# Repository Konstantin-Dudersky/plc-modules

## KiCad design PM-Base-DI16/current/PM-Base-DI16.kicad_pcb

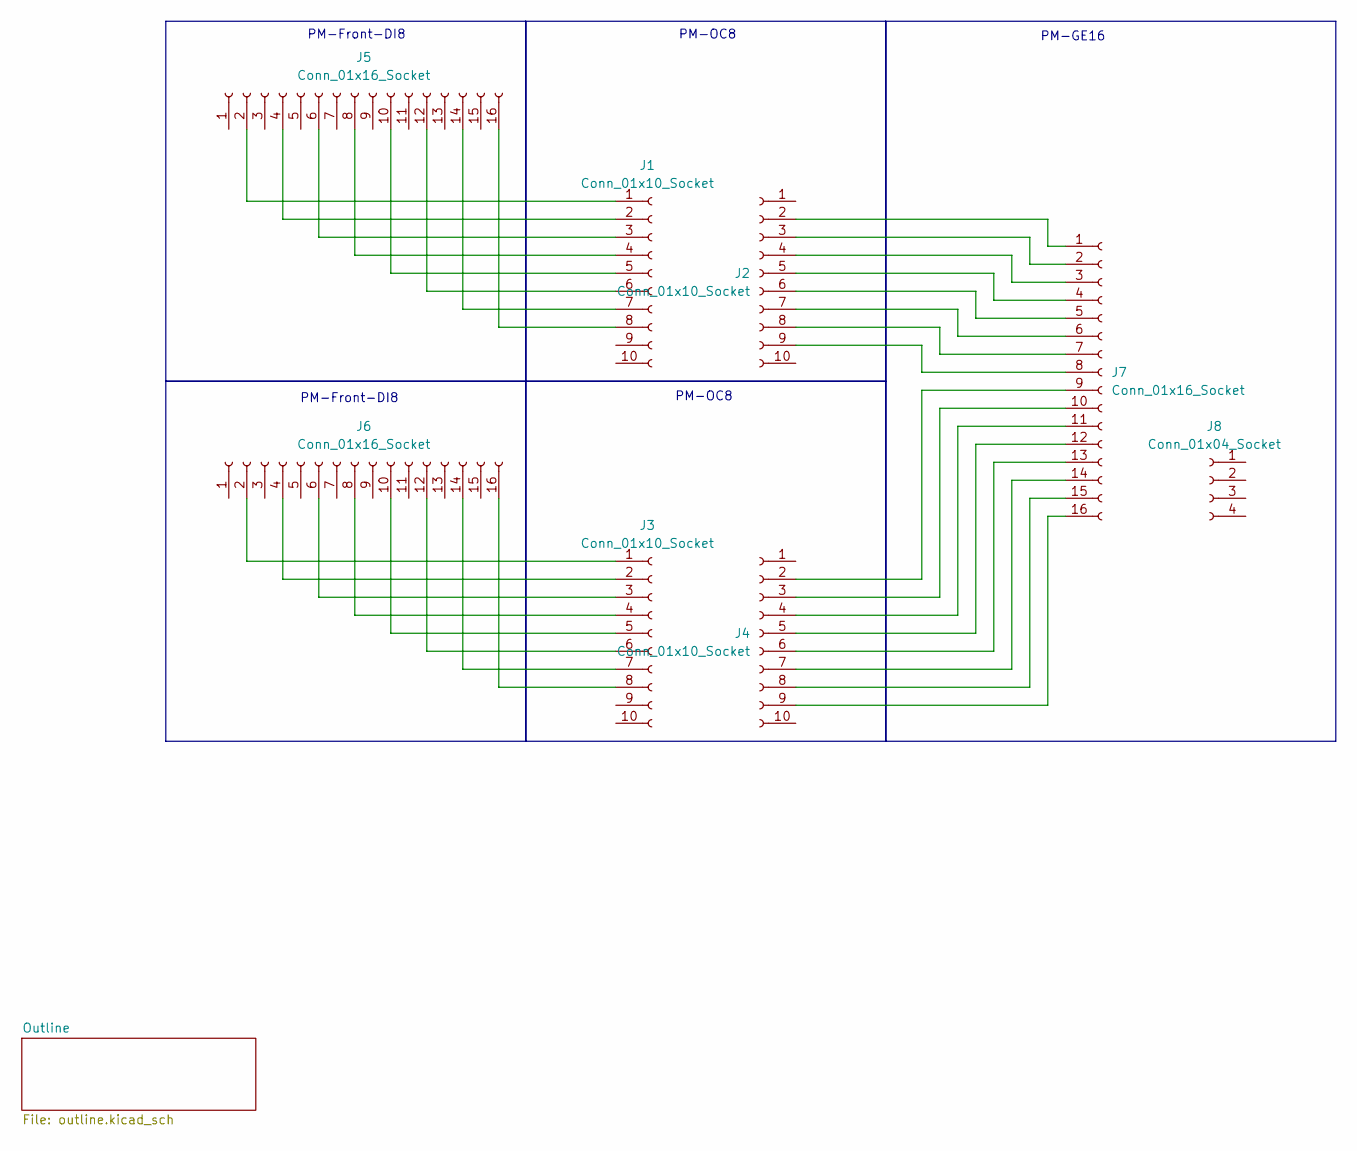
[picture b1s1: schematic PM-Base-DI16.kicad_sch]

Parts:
J1, J2, J3, J4: Conn_01x10_Socket; PinSocket_1x10_P2.54mm_Vertical_SMD_Pin1Left
J5, J6, J7: Conn_01x16_Socket; PinSocket_1x16_P2.54mm_Vertical_SMD_Pin1Left
J8: Conn_01x04_Socket; PinSocket_1x04_P2.54mm_Vertical_SMD_Pin1Left

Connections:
unnamed: J1.1, J5.2
unnamed: J1.2, J5.4
unnamed: J1.3, J5.6
unnamed: J1.4, J5.8
unnamed: J1.5, J5.10
unnamed: J1.6, J5.12
unnamed: J1.7, J5.14
unnamed: J1.8, J5.16
unnamed: J2.2, J7.1
unnamed: J2.3, J7.2
unnamed: J2.4, J7.3
unnamed: J2.5, J7.4
unnamed: J2.6, J7.5
unnamed: J2.7, J7.6
unnamed: J2.8, J7.7
unnamed: J2.9, J7.8
unnamed: J3.1, J6.2
unnamed: J3.2, J6.4
unnamed: J3.3, J6.6
unnamed: J3.4, J6.8
unnamed: J3.5, J6.10
unnamed: J3.6, J6.12
unnamed: J3.7, J6.14
unnamed: J3.8, J6.16
unnamed: J4.2, J7.9
unnamed: J4.3, J7.10
unnamed: J4.4, J7.11
unnamed: J4.5, J7.12
unnamed: J4.6, J7.13
unnamed: J4.7, J7.14
unnamed: J4.8, J7.15
unnamed: J4.9, J7.16

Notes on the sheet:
PM-OC8
PM-Front-DI8
PM-GE16

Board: 2 copper layers, 8 parts (0 on the bottom side), 32 nets, no tracks yet.

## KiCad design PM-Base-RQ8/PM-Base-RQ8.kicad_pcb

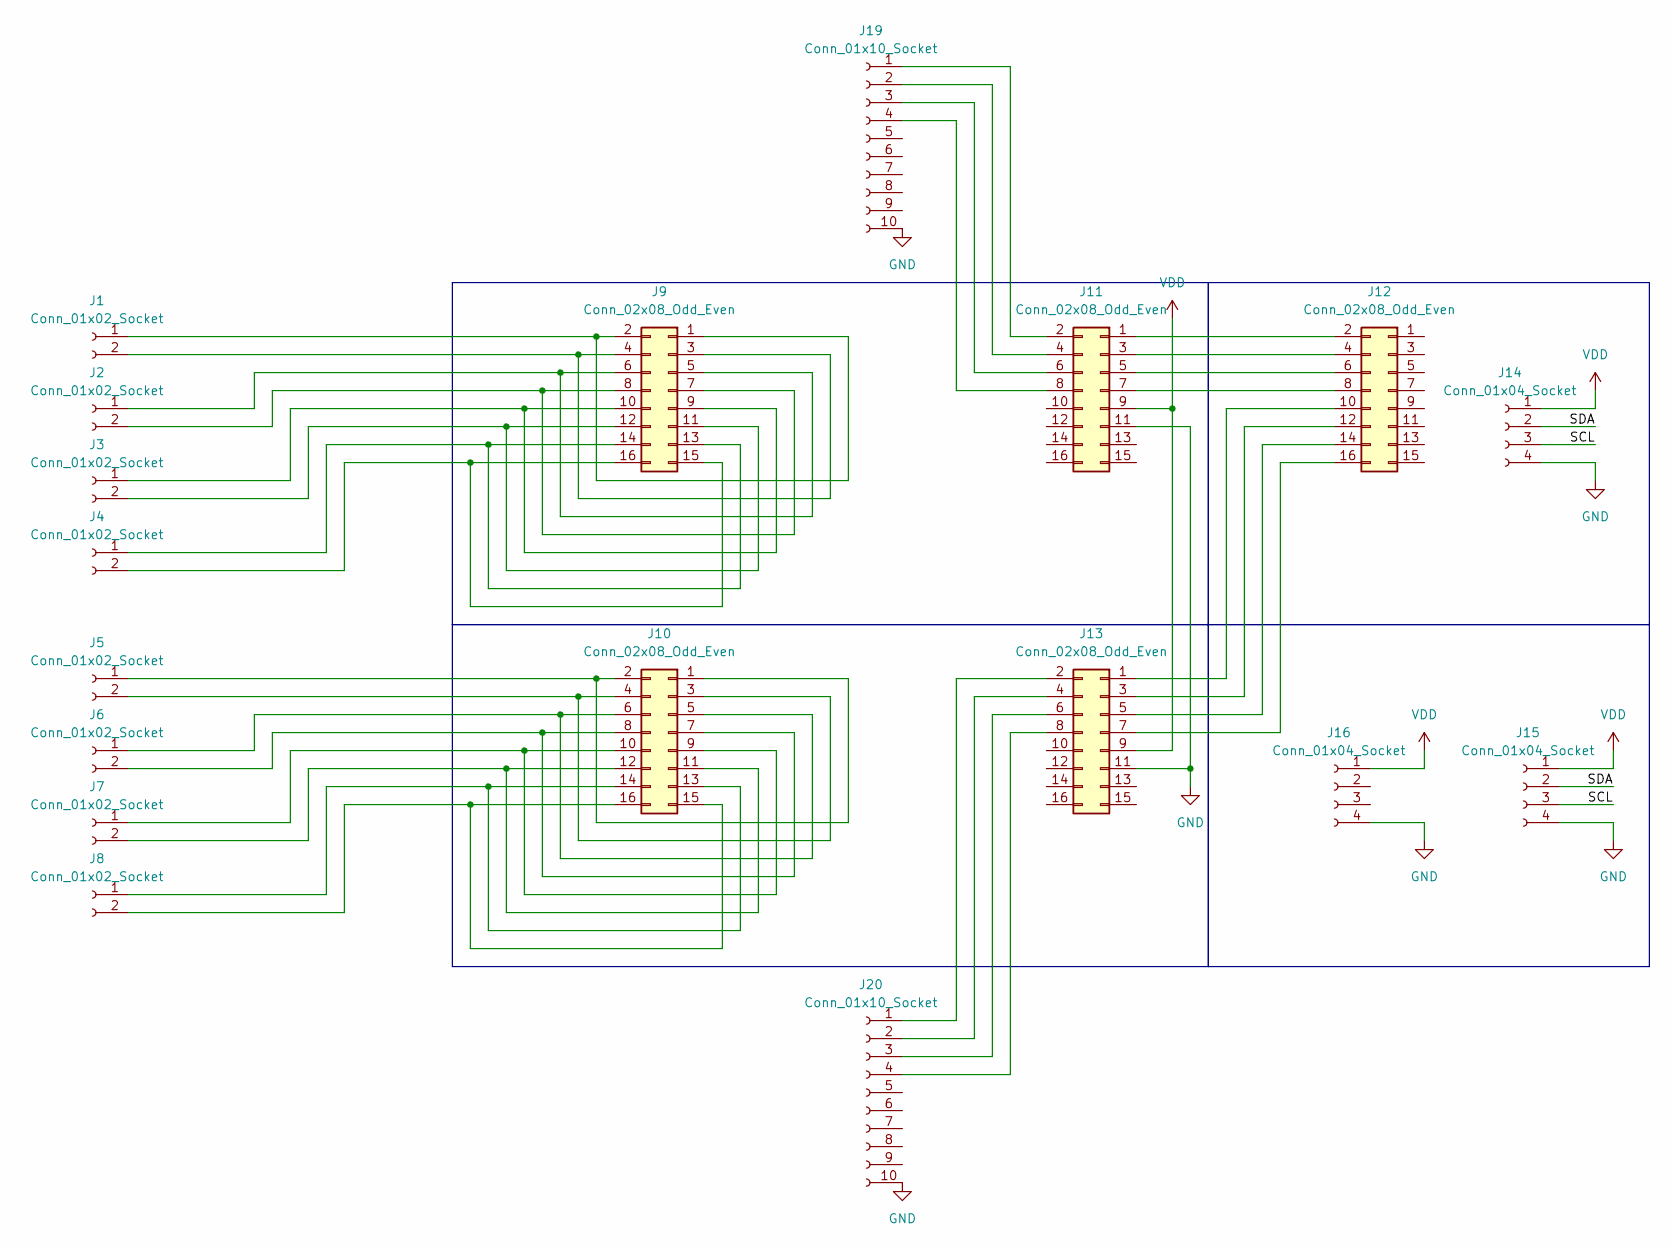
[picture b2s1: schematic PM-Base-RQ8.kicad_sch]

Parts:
J1, J2, J3, J4, J5, J6, J7, J8: Conn_01x02_Socket; Degson_2EDGK-5.08-02P
J9, J10, J11, J12, J13: Conn_02x08_Odd_Even; PinSocket_2x08_P2.54mm_Vertical_SMD
J14, J15, J16: Conn_01x04_Socket; PinSocket_1x04_P2.54mm_Vertical_SMD_Pin1Left
J19, J20: Conn_01x10_Socket; PinSocket_1x10_P2.54mm_Vertical_SMD_Pin1Left

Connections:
/SCL: J14.3, J15.3
/SDA: J14.2, J15.2
GND: J11.11, J13.11, J14.4, J15.4, J16.4, J19.10, J20.10
unnamed: J1.1, J9.1, J9.2
unnamed: J1.2, J9.3, J9.4
unnamed: J2.1, J9.5, J9.6
unnamed: J2.2, J9.7, J9.8
unnamed: J3.1, J9.9, J9.10
unnamed: J3.2, J9.11, J9.12
unnamed: J4.1, J9.13, J9.14
unnamed: J4.2, J9.15, J9.16
unnamed: J5.1, J10.1, J10.2
unnamed: J5.2, J10.3, J10.4
unnamed: J6.1, J10.5, J10.6
unnamed: J6.2, J10.7, J10.8
unnamed: J7.1, J10.9, J10.10
unnamed: J7.2, J10.11, J10.12
unnamed: J8.1, J10.13, J10.14
unnamed: J8.2, J10.15, J10.16
unnamed: J11.1, J12.2
unnamed: J11.2, J19.1
unnamed: J11.3, J12.4
unnamed: J11.4, J19.2
unnamed: J11.5, J12.6
unnamed: J11.6, J19.3
unnamed: J11.7, J12.8
unnamed: J11.8, J19.4
unnamed: J12.10, J13.1
unnamed: J12.12, J13.3
unnamed: J12.14, J13.5
unnamed: J12.16, J13.7
unnamed: J13.2, J20.1
unnamed: J13.4, J20.2
unnamed: J13.6, J20.3
unnamed: J13.8, J20.4
VDD: J11.9, J13.9, J14.1, J15.1, J16.1

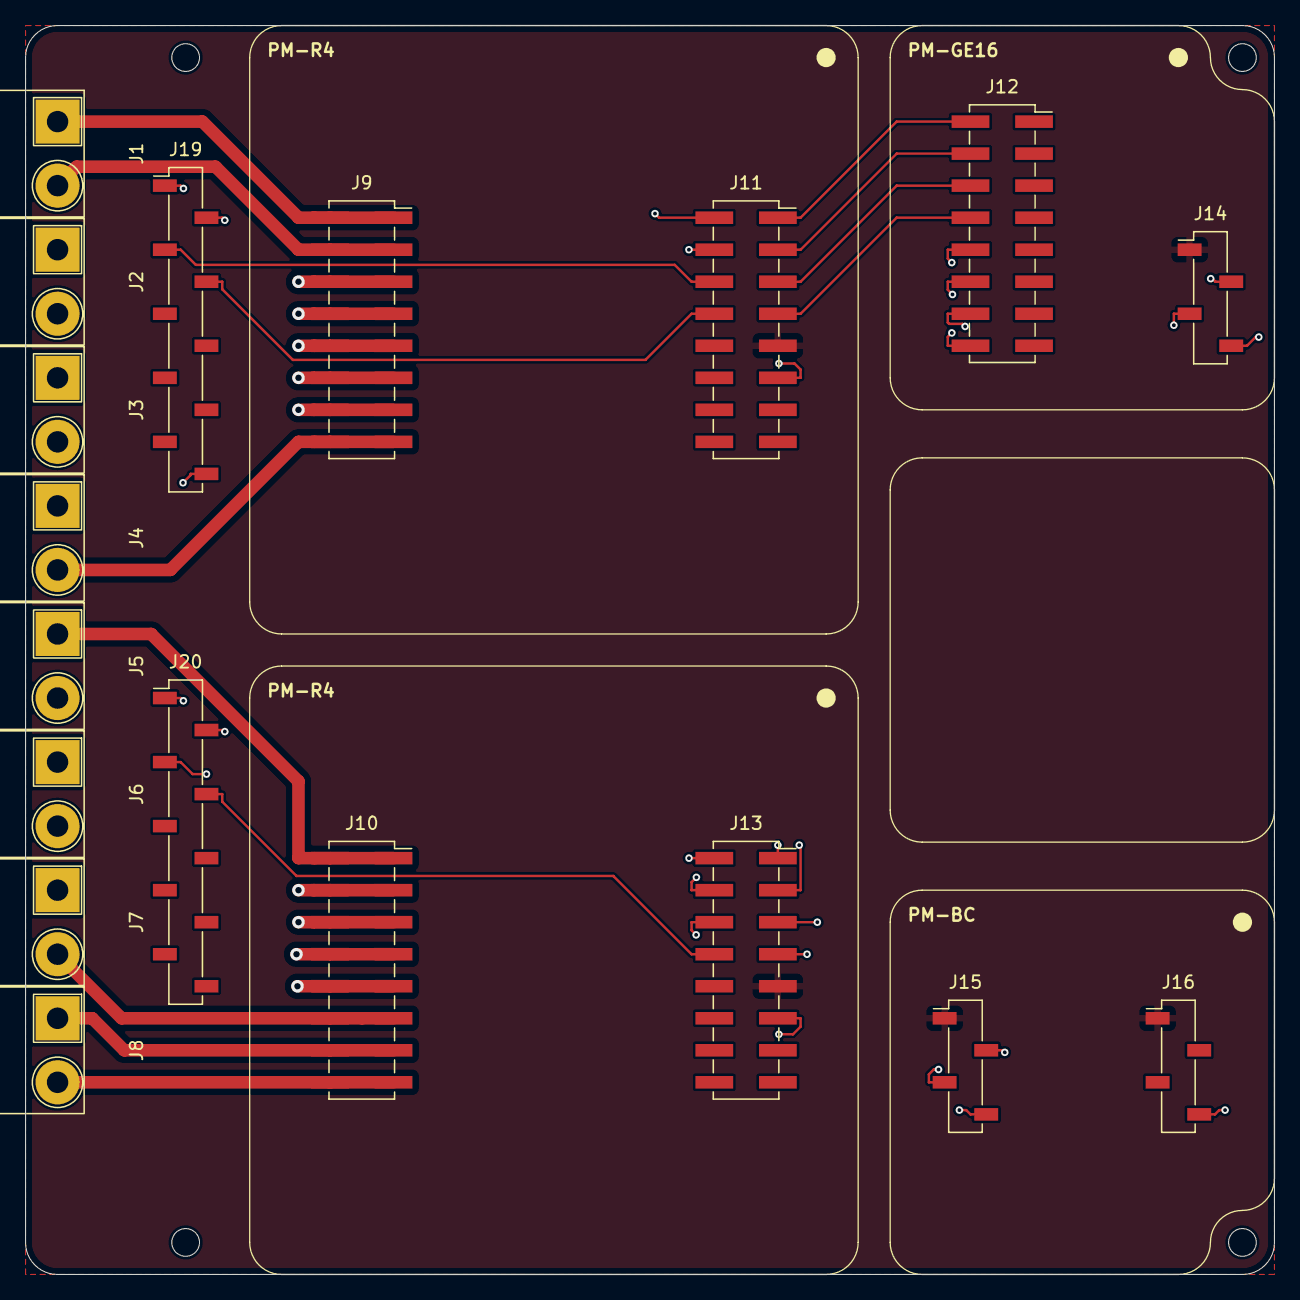
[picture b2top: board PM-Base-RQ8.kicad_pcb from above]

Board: 4 copper layers, 99.1 x 99.1 mm, 22 parts (0 on the bottom side), 36 nets.

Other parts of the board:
H1, H2, H3, H4: MountingHole_2.2mm_M2

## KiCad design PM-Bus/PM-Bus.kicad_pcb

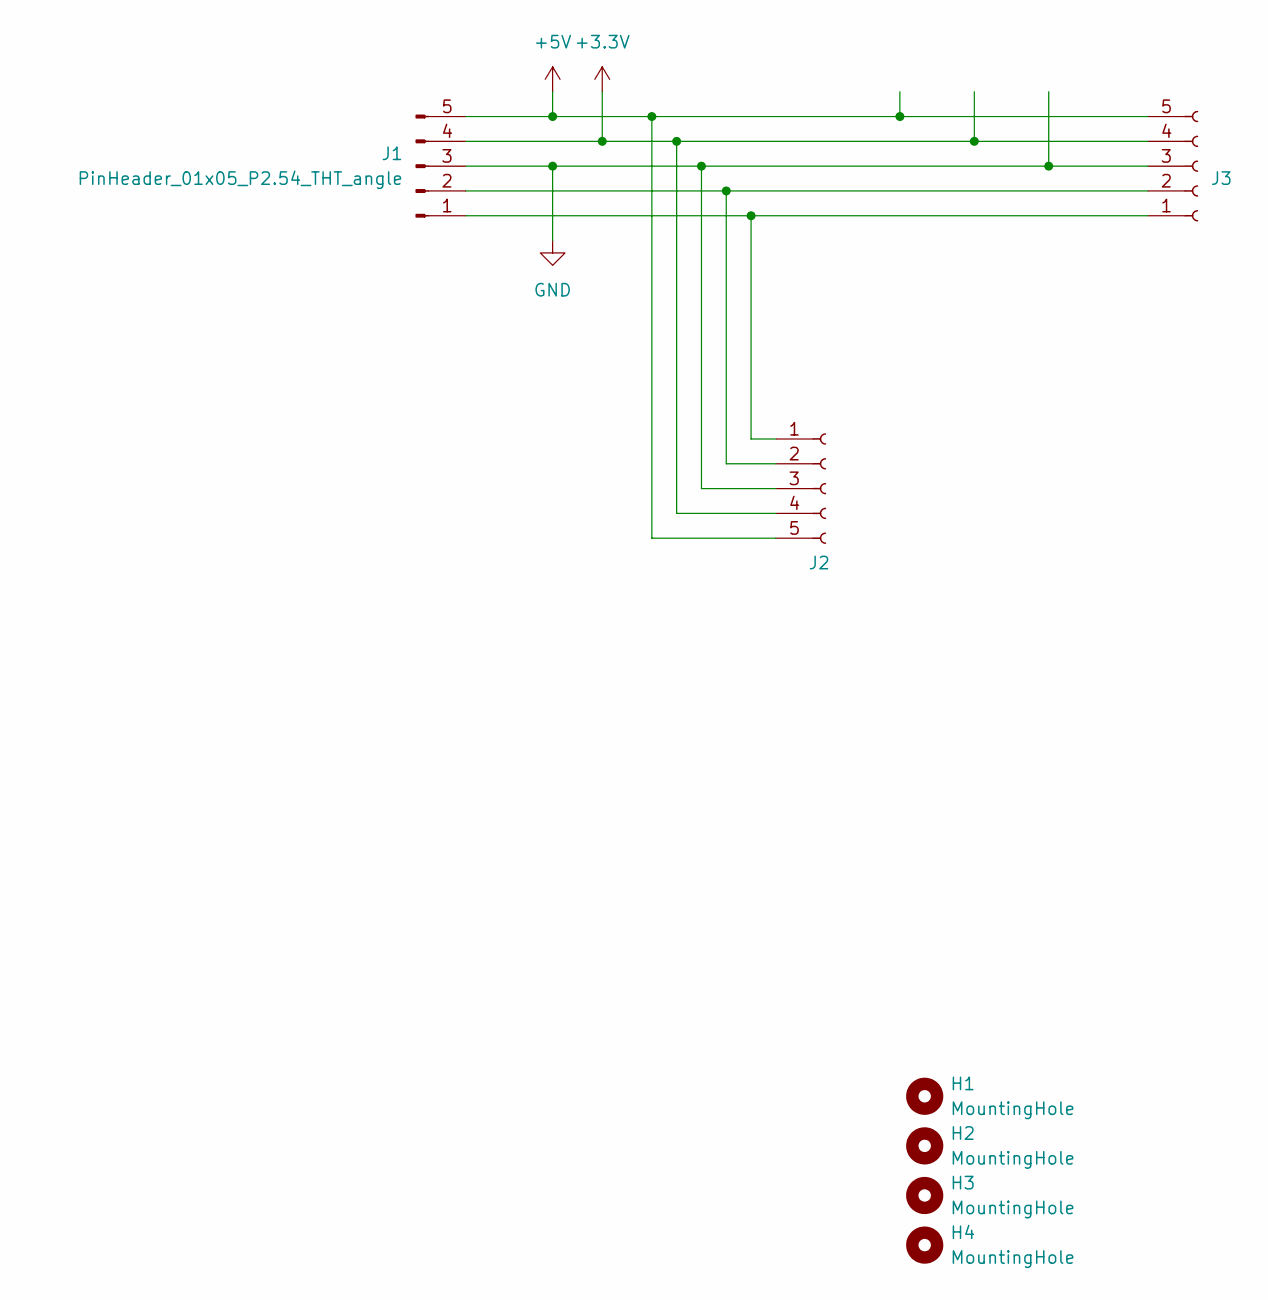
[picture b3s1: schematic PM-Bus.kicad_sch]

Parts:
H1, H2, H3, H4: MountingHole; MountingHole_3.2mm_M3
J1: PinHeader_01x05_P2.54_THT_angle; PinHeader_1x05_P2.54mm_Horizontal; part_ipn PinHeader_01x05_P2.54_THT_angle
J2: FemaleHeader_01x05_P2.54_THT_straight; PinSocket_1x05_P2.54mm_Vertical; part_ipn FemaleHeader_01x05_P2.54_THT_straight
J3: FemaleHeader_01x05_P2.54_THT_angle; PinSocket_1x05_P2.54mm_Horizontal; part_ipn FemaleHeader_01x05_P2.54_THT_angle

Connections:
+3.3V: J1.4, J2.4, J3.4
+5V: J1.5, J2.5, J3.5
GND: J1.3, J2.3, J3.3
unnamed: J1.1, J2.1, J3.1
unnamed: J1.2, J2.2, J3.2

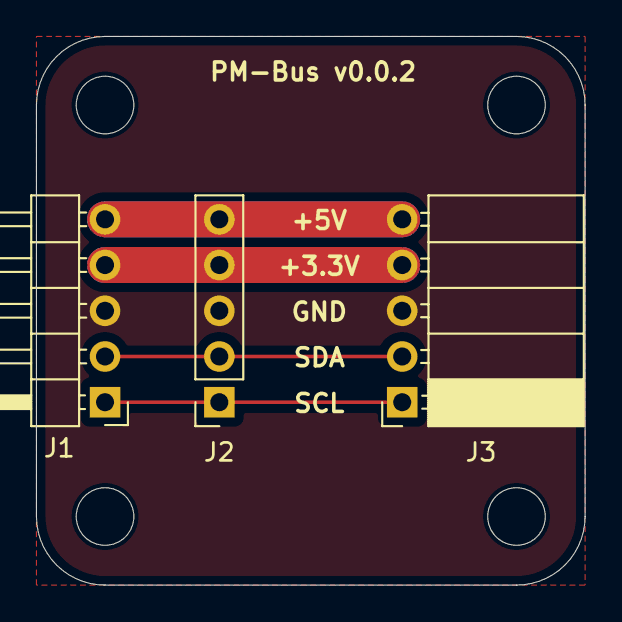
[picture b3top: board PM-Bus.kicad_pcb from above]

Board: 2 copper layers, 30.5 x 30.5 mm, 8 parts (1 on the bottom side), 5 nets.

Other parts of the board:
Logo_kicad: KiCad-Logo2_5mm_SilkScreen

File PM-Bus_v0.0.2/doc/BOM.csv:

"reference","note","quantity","part_ipn"
"J1","Generic connector, single row, 01x05, script generated","1","PinHeader_01x05_P2.54_THT_angle"
"J2","Generic connector, single row, 01x05, script generated","1","FemaleHeader_01x05_P2.54_THT_straight"
"J3","Generic connector, single row, 01x05, script generated","1","FemaleHeader_01x05_P2.54_THT_angle"

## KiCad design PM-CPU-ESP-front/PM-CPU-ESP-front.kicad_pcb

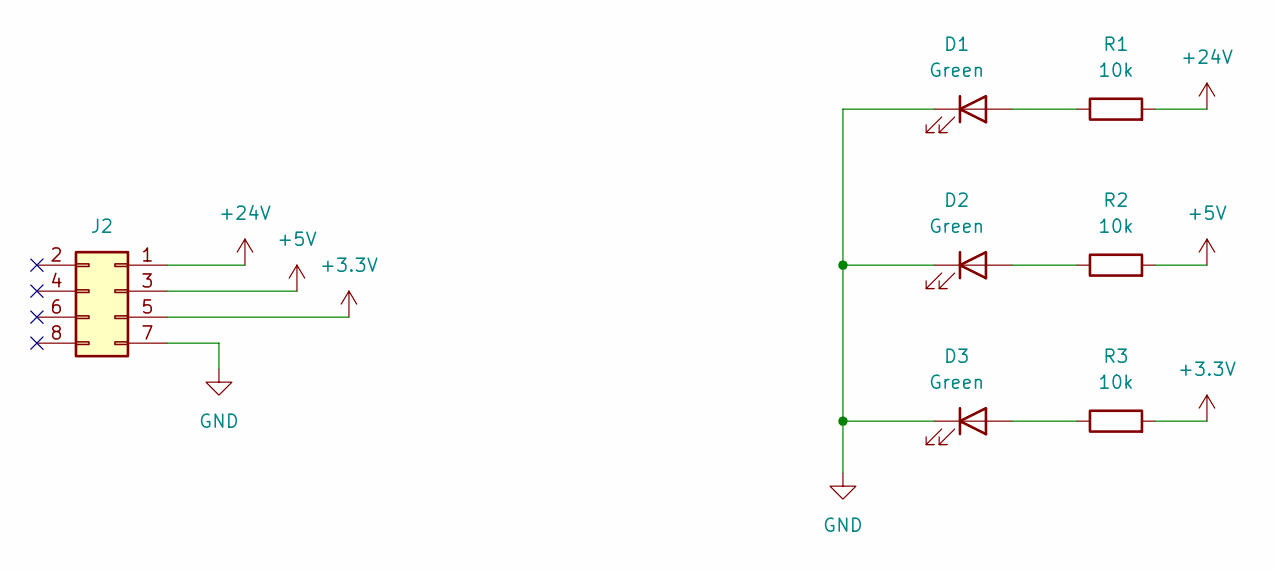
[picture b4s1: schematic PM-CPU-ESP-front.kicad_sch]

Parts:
D1, D2, D3: Green; LED_1206_3216Metric_ReverseMount_Hole1.8x2.4mm; part_ipn LED_green_1206_reverse
J2: PinHeader_02x04_P2.54_THT_angle; PinHeader_2x04_P2.54mm_Horizontal; part_ipn PinHeader_02x04_P2.54_THT_angle
R1, R2, R3: 10k; R_1206_3216Metric_Pad1.30x1.75mm_HandSolder; part_ipn R_10k_1206_1%

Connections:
+3.3V: J2.5, R3.2
+5V: J2.3, R2.2
+24V: J2.1, R1.2
GND: D1.1 (K), D2.1 (K), D3.1 (K), J2.7
unnamed: D1.2 (A), R1.1
unnamed: D2.2 (A), R2.1
unnamed: D3.2 (A), R3.1

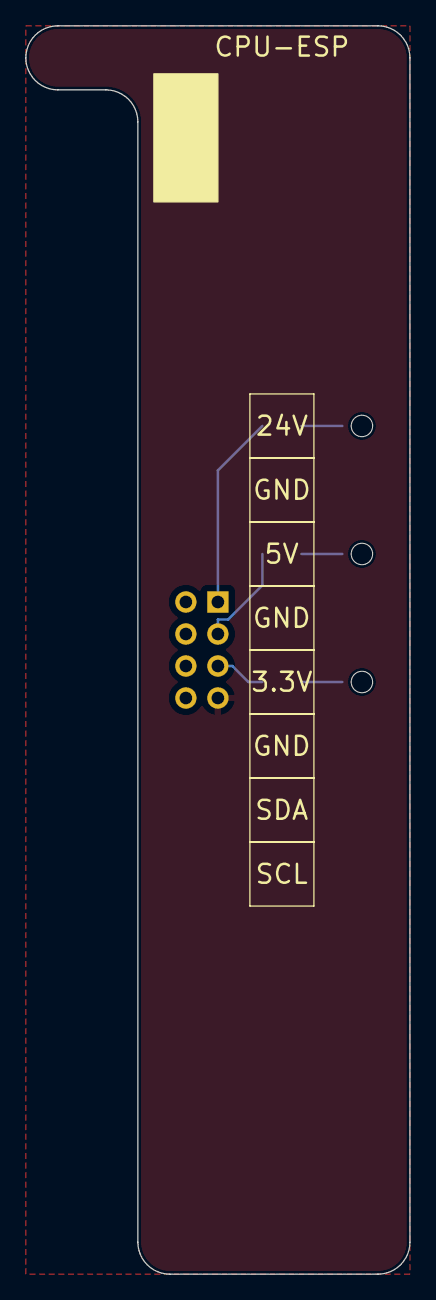
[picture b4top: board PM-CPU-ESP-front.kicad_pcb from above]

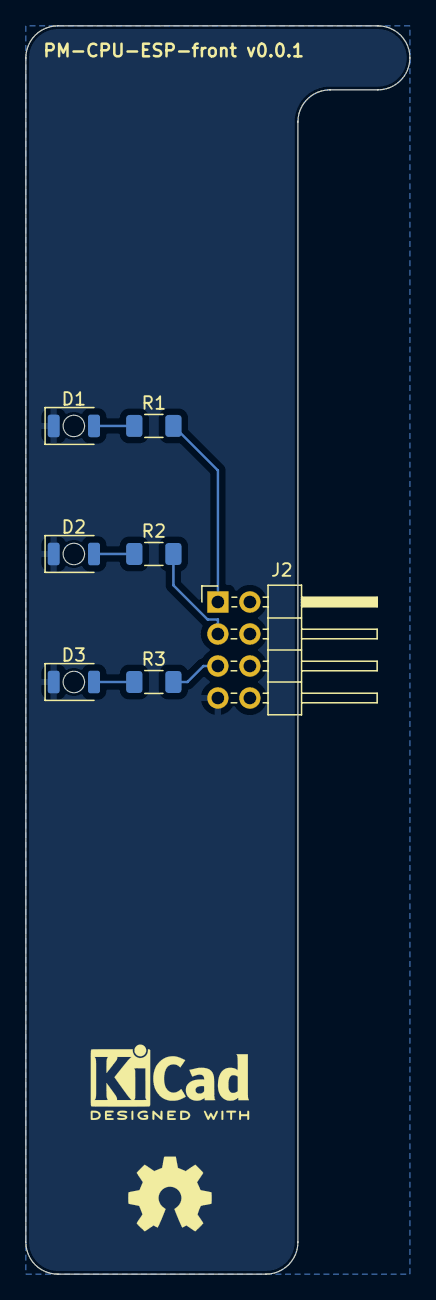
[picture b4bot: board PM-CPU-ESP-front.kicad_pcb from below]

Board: 2 copper layers, 30.5 x 99.1 mm, 8 parts (8 on the bottom side), 7 nets.

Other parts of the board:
Logo_kicad: KiCad-Logo2_5mm_SilkScreen

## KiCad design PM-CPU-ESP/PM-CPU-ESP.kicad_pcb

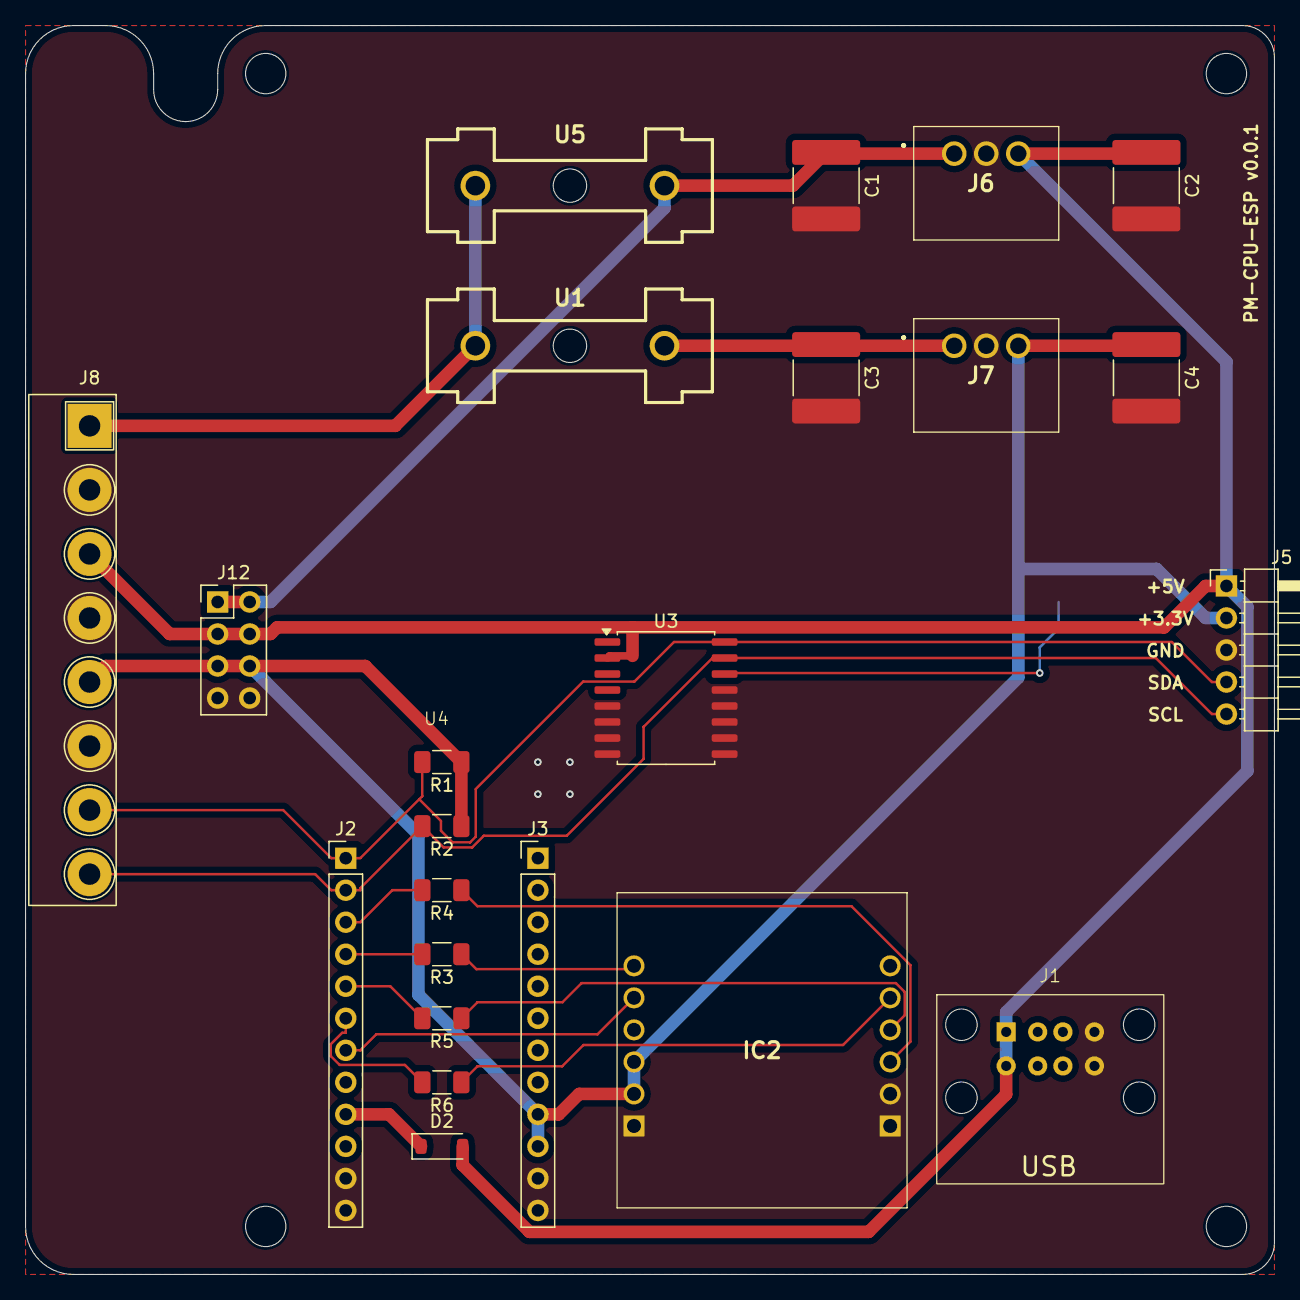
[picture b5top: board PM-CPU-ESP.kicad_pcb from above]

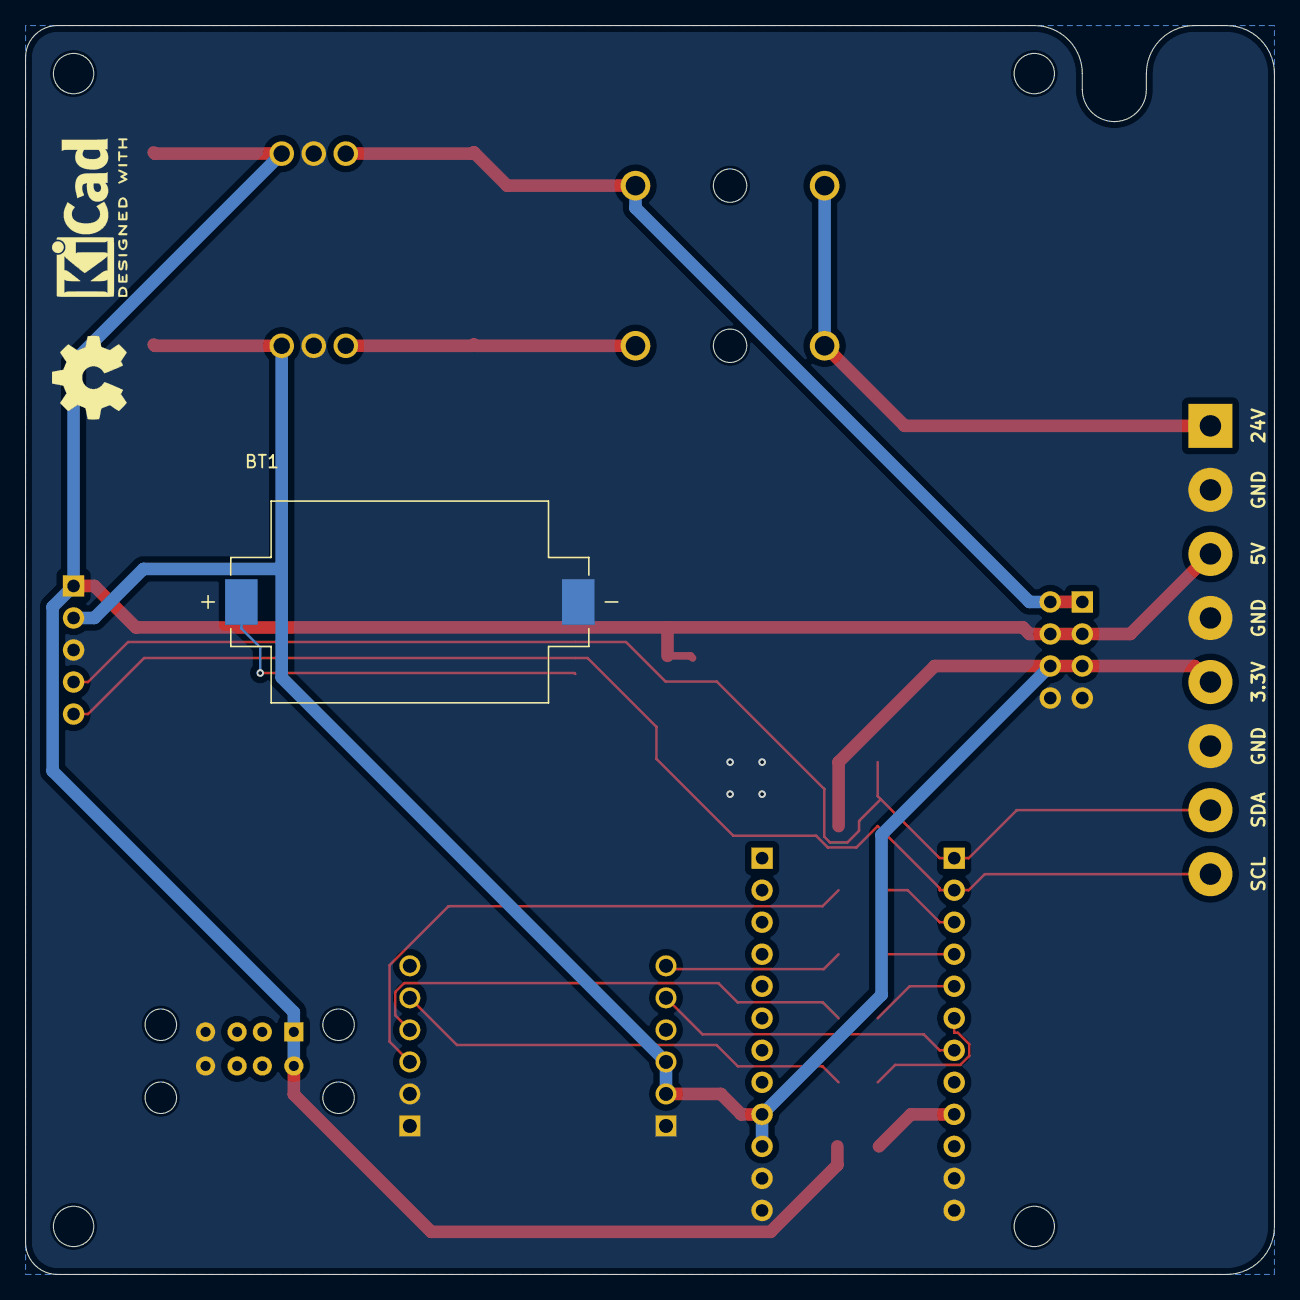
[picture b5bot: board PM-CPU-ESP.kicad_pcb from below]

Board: 2 copper layers, 99.1 x 99.1 mm, 31 parts (3 on the bottom side), 19 nets.

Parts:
BT1: 1060TR; Keystone_1060TR
C1, C2, C3, C4: 22uF; C_2220_5750Metric_Pad1.97x5.40mm_HandSolder
D2: B5819W; D_SOD-123
H1, H2, H3, H4: MountingHole; MountingHole_3.2mm_M3
IC2: USR-ES1; USRES1
J1: XKB_U224-08XN-1WR61
J2, J3: PinHeader P2.54 01x12 THT Straight; PinHeader_1x12_P2.54mm_Vertical
J5: PinHeader_01x05_P2.54_THT_angle; PinHeader_1x05_P2.54mm_Horizontal
J6: K7805-2000R3
J7: K7803-2000R3; K7805-2000R3
J8: 2EDGR-5.08-08P; Degson_2EDGR-5.08-08P
J12: PM-front-02x04
R1, R2: 3k3; R_1206_3216Metric_Pad1.30x1.75mm_HandSolder
R3, R4, R5, R6: 100; R_1206_3216Metric_Pad1.30x1.75mm_HandSolder
U1, U5: 64900001039; Fuseholder
U3: DS3231; SOIC-16W_7.5x10.3mm_P1.27mm
U4: ESP32-C3; Weact ESP32-C3FH4
kicad_logo: KiCad-Logo2_5mm_SilkScreen
oshw_logo: OSHW-Symbol_6.7x6mm_SilkScreen

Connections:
+3.3V: C4.1, IC2.B2 (3V3_1), IC2.B3 (3V3_2), J3.9, J3.10, J5.2, J7.3 (+VO), J8.5, J12.5, J12.6, R1.1, R2.1
+5V: C2.1, D2.2 (A), J1.1 (5V), J1.5 (5V), J5.1, J6.3 (+VO), J8.3, J12.3, J12.4, U3.2 (VCC)
+24V: C1.1, J6.1 (VIN), J12.1, J12.2, U5.2
/24V_IN: J8.1, U1.1, U5.1
/CLK: IC2.A4 (SCLK), R5.1
/CS: IC2.A5 (CS), R6.1
/MISO: J2.4, R3.2
/MOSI: IC2.A3 (MOSI), R4.1
/RST: IC2.B5 (RST), J2.7
/SCL: J2.2, J5.5, J8.8, R2.2, U3.15 (SDA)
/SDA: J2.1, J5.4, J8.7, R1.2, U3.16 (SCL)
GND: BT1.N, C1.2, C2.2, C3.2, C4.2, IC2.A1 (GND_1), IC2.A2 (GND_2), IC2.B1 (GND_3), J1.4 (GND), J1.8 (GND), J2.11, J2.12, J3.11, J3.12, J5.3, J6.2 (GND), J7.2 (GND), J8.2, J8.4, J8.6, J12.7, J12.8, U3.5 (GND), U3.6 (GND), U3.7 (GND), U3.8 (GND), U3.9 (GND), U3.10 (GND), U3.11 (GND), U3.12 (GND), U3.13 (GND)
unnamed: D2.1 (K), J2.9
unnamed: IC2.B6 (MISO), R3.1
unnamed: J2.3, R4.2
unnamed: J2.5, R5.2
unnamed: J2.6, R6.2
unnamed: C3.1, J7.1 (VIN), U1.2
unnamed: BT1.P, U3.14 (VBAT)
